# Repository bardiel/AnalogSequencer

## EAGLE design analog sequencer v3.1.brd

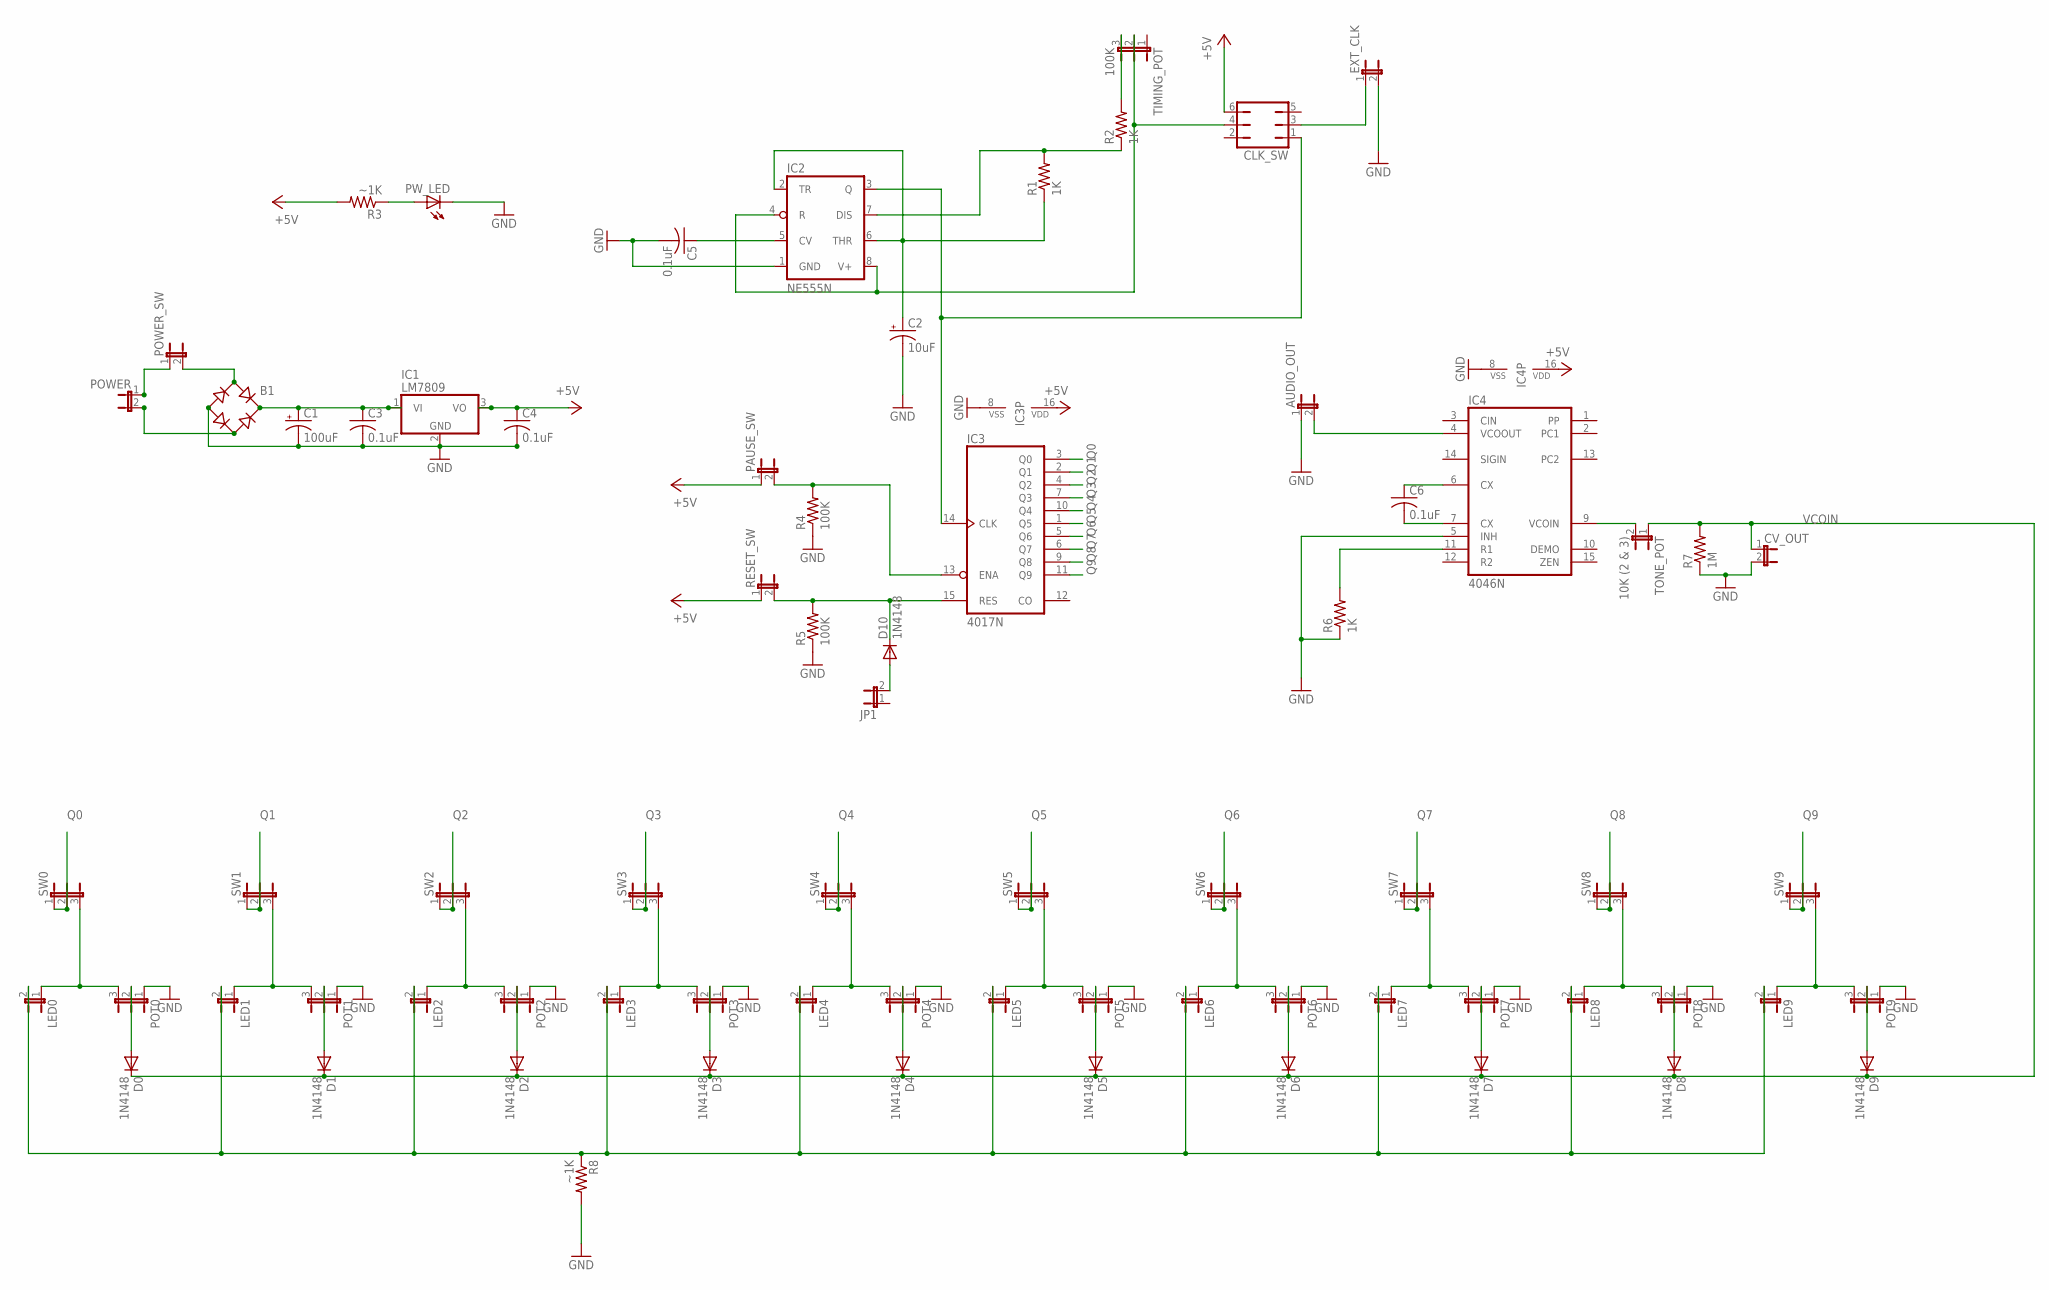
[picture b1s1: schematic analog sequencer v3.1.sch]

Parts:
AUDIO_OUT: JP1E; JP1
B1: RECTIFIER-RB1A; RB1A
C1: 100uF; E2,5-5
C2: 10uF; E2,5-5
C3, C4, C5, C6: 0.1uF; C025-025X050
CLK_SW: JP3Q
CV_OUT: JP1E; JP1
D0, D1, D2, D3, D4, D5, D6, D7, D8, D9, D10: 1N4148; DO35-7
EXT_CLK: JP1E; JP1
IC1: LM7809; TO220V
IC2: NE555N; DIL08
IC3: 4017N; DIL16
IC4: 4046N; DIL16
JP1: JP1E; JP1
LED0, LED1, LED2, LED3, LED4, LED5, LED6, LED7, LED8, LED9: JP1E; JP1
PAUSE_SW: JP1E; JP1
POT0, POT1, POT2, POT3, POT4, POT5, POT6, POT7, POT8, POT9: JP2E; JP2
POWER: JP1E; JP1
POWER_SW: JP1E; JP1
PW_LED: LED5MM
R1, R2, R6: 1K; 0204/7
R3, R8: ~1K; 0204/7
R4, R5: 100K; 0204/7
R7: 1M; 0204/7
RESET_SW: JP1E; JP1
SW0, SW1, SW2, SW3, SW4, SW5, SW6, SW7, SW8, SW9: JP2E; JP2
TIMING_POT: 100K; JP2
TONE_POT: 10K (2 & 3); JP1

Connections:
+5V: C4.1, CLK_SW.6, IC1.3 (VO), IC3.16 (VDD), IC4.16 (VDD), PAUSE_SW.1, R3.2, RESET_SW.1
GND: AUDIO_OUT.1, B1.-, C1.-, C2.-, C3.2, C4.2, C5.2, CV_OUT.2, EXT_CLK.2, IC1.2 (GND), IC2.1 (GND), IC3.8 (VSS), IC4.5 (INH), IC4.8 (VSS), POT0.1, POT1.1, POT2.1, POT3.1, POT4.1, POT5.1, POT6.1, POT7.1, POT8.1, POT9.1, PW_LED.K (C), R4.1, R5.1, R6.1, R7.1, R8.2
unnamed: B1.AC2, POWER.2
unnamed: B1.AC1, POWER_SW.2
unnamed: POWER.1, POWER_SW.1
unnamed: C5.1, IC2.5 (CV)
unnamed: CLK_SW.1, IC2.3 (Q), IC3.14 (CLK)
unnamed: R2.2, TIMING_POT.3
unnamed: B1.+, C1.+, C3.1, IC1.1 (VI)
unnamed: IC2.7 (DIS), R1.2, R2.1
unnamed: CLK_SW.4, IC2.4 (R), IC2.8 (V+), TIMING_POT.2
unnamed: C2.+, IC2.2 (TR), IC2.6 (THR), R1.1
unnamed: CLK_SW.3, EXT_CLK.1
unnamed: LED0.1, POT0.3, SW0.3
unnamed: LED1.1, POT1.3, SW1.3
unnamed: LED2.1, POT2.3, SW2.3
unnamed: LED3.1, POT3.3, SW3.3
unnamed: LED4.1, POT4.3, SW4.3
unnamed: LED5.1, POT5.3, SW5.3
unnamed: LED6.1, POT6.3, SW6.3
unnamed: LED7.1, POT7.3, SW7.3
unnamed: LED8.1, POT8.3, SW8.3
unnamed: LED9.1, POT9.3, SW9.3
unnamed: IC3.13 (ENA), PAUSE_SW.2, R4.2
unnamed: LED0.2, LED1.2, LED2.2, LED3.2, LED4.2, LED5.2, LED6.2, LED7.2, LED8.2, LED9.2, R8.1
unnamed: D10.A, JP1.2
unnamed: IC4.9 (VCOIN), TONE_POT.2
unnamed: D0.A, POT0.2
unnamed: D1.A, POT1.2
unnamed: D2.A, POT2.2
unnamed: D3.A, POT3.2
unnamed: D4.A, POT4.2
unnamed: D5.A, POT5.2
unnamed: D6.A, POT6.2
unnamed: D7.A, POT7.2
unnamed: D8.A, POT8.2
unnamed: D9.A, POT9.2
unnamed: C6.1, IC4.6 (CX)
unnamed: C6.2, IC4.7 (CX)
unnamed: IC4.11 (R1), R6.2
unnamed: AUDIO_OUT.2, IC4.4 (VCOOUT)
unnamed: PW_LED.A, R3.1
Q0: IC3.3 (Q0), SW0.1, SW0.2
Q1: IC3.2 (Q1), SW1.1, SW1.2
Q2: IC3.4 (Q2), SW2.1, SW2.2
Q3: IC3.7 (Q3), SW3.1, SW3.2
Q4: IC3.10 (Q4), SW4.1, SW4.2
Q5: IC3.1 (Q5), SW5.1, SW5.2
Q6: IC3.5 (Q6), SW6.1, SW6.2
Q7: IC3.6 (Q7), SW7.1, SW7.2
Q8: IC3.9 (Q8), SW8.1, SW8.2
Q9: IC3.11 (Q9), SW9.1, SW9.2
RESET: D10.C, IC3.15 (RES), R5.2, RESET_SW.2
VCOIN: CV_OUT.1, D0.C, D1.C, D2.C, D3.C, D4.C, D5.C, D6.C, D7.C, D8.C, D9.C, R7.2, TONE_POT.1

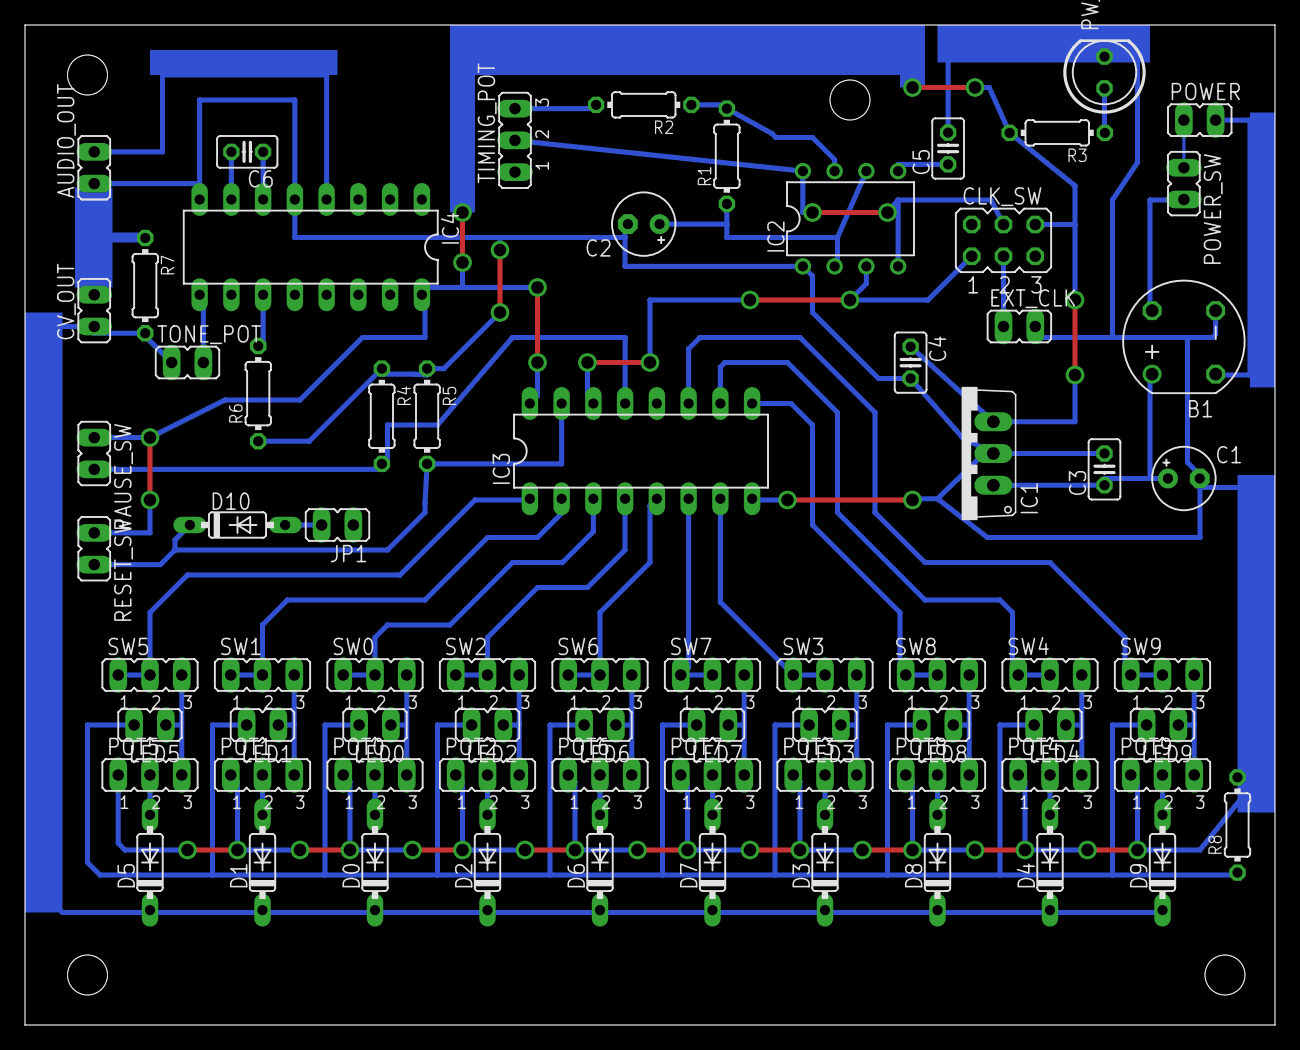
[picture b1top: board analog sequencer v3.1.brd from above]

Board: 2 copper layers, 100.0 x 80.0 mm, 72 parts (0 on the bottom side), 54 nets.
